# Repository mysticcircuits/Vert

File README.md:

# Vert
files for the Vert Eurorack module by Mystic Circuits.

This module comes with an open source licence, CC-BY-SA 3.0.  Go ahead and read the licence page for more details. This means that there are no commercial restrictions on this module.  Please be reasonable in your interpretation of this rule.  I fully support people building their own circuit boards and even trading amongst their friends for them.  However organizing group buys for these PCBs or selling the PCBs on your own will compete directly with my own products, since I sell PCBs on my website and also provide the build documentation and support.  In short - don't be a shmuck about it or else I will stop open sourcing my designs.

Also note that this module is made to function with my "Universal Front Plate" PCB which is hosted in another branch.  It can make the schematic a bit tricky to read sometimes but I did my best to annotate things.  There *might* be some inconsistencies between the pin naming convention for this schematic and the one on the "UFP" schematic because this was the first circuit that I build to work with the UFP and they both went through several revisions together.

For a description of the licence in simple terms please visit https://creativecommons.org/licenses/by-sa/3.0/

*************************************************************************************BUILD INSTRUCTIONS

Here is a link to the instructions.  Please look them over before you attempt to build a Vert and make sure that it is within your skill level.  The Vert is an intermediate build and involves SMD soldering.  I would definitely not attempt to build it as your first project.

https://drive.google.com/file/d/0B1jw1Qp2qZVJNUZ4QTZxX2lhblk/view?usp=sharing

Here is a link to the mouser cart.  Please note that it does not include several components and is also designed to build a VERT with all white LEDs.  Also be aware that I have noticed different behavior between different 555 timer IC models, the model included in the cart is the one that I use because it is stable.

http://www.mouser.com/ProjectManager/ProjectDetail.aspx?AccessID=2263e5f92d

There are two sources for the hardware, unfortunately you can not buy all of what you need from either place:

For the jacks go to either Thonk or Modular Addict.  You need 11 of the the "erthenvar" aka PJ301BM jacks.  Make sure to get nuts along with them, you might have to buy them separately.  Knurled or hex are both fine it's up to you.

https://www.thonk.co.uk/shop/3-5mm-jacks/

https://modularaddict.com/parts/jacks/pj301bm-jacks

You can also buy the vertical PCB mount alpha pots from Thonk/ Modularaddict or Small Bear.  Its way cheaper than buying them from Mouser

1M LINEAR POT x1

100K LINEAR POT x2

https://www.thonk.co.uk/shop/alpha-9mm-pots/

https://modularaddict.com/parts/potentiometers-1/9mm-potentiometers

http://smallbear-electronics.mybigcommerce.com/alpha-single-gang-9mm-right-angle-pc-mount/

Here are the links for the Small Bear parts.  You can buy SPDT switches from a variety of places but I highly suggest buying the short bat toggles listed below.  The switches go in between the pots and so if the bats are too long they will interfere with your ability to turn the knobs comfortably.  I haven't personally tried the Tayda toggle switches but see no reason that they wouldn't work.  If you try them out please let me know how it goes so I can confirm whether or not they are a good choice.

http://smallbear-electronics.mybigcommerce.com/spdt-on-on-0218b/

https://www.taydaelectronics.com/electromechanical/switches-key-pad/toggle-switch/mini-toggle-switch-1m-series-spdt-on-on-short-lever.html

I also buy my purple knobs from Small Bear but any knobs that fit a smooth pot shaft will do.  If you want to use knobs for knurled or D-pot shafts obviously you just have to find the corresponding shaft to replace mine.  I like these pots because they are thin, the painted indicator is inlayed so it wont rub off, and the knurl feels good on the finger.

http://smallbear-electronics.mybigcommerce.com/knurled-silver-center-colors/

https://www.thonk.co.uk/shop/knobs-davies-1900h-clone-metal/

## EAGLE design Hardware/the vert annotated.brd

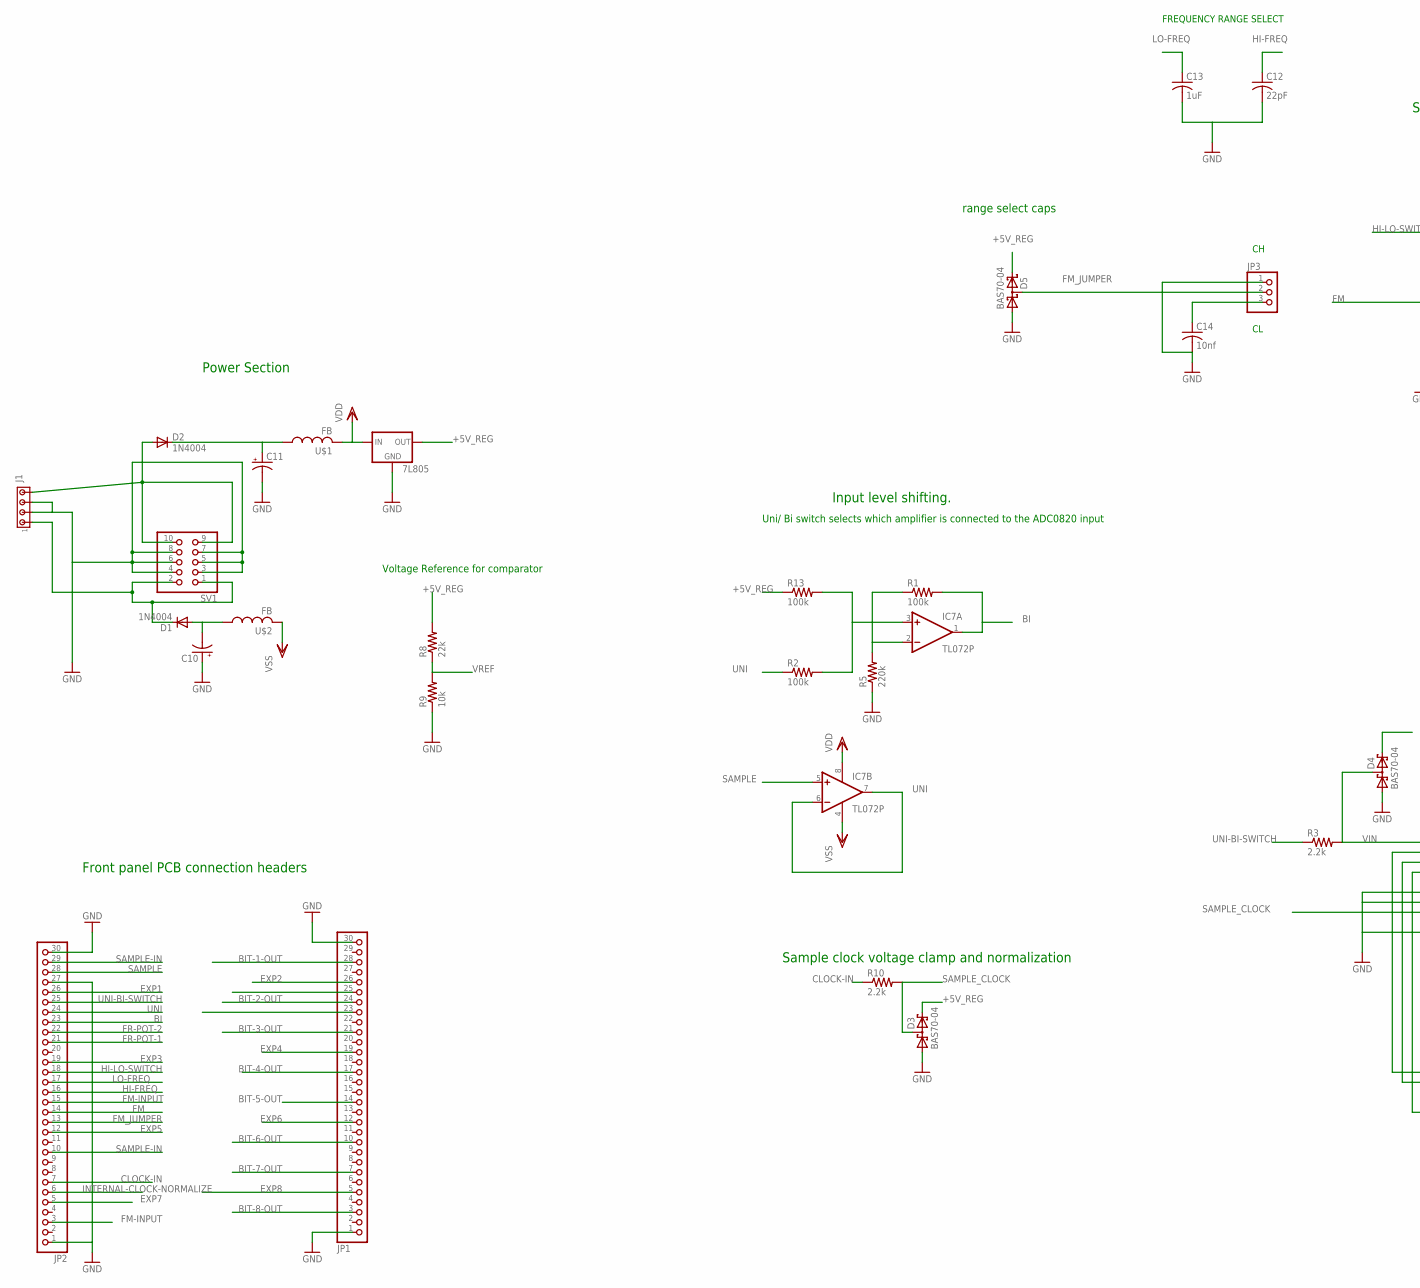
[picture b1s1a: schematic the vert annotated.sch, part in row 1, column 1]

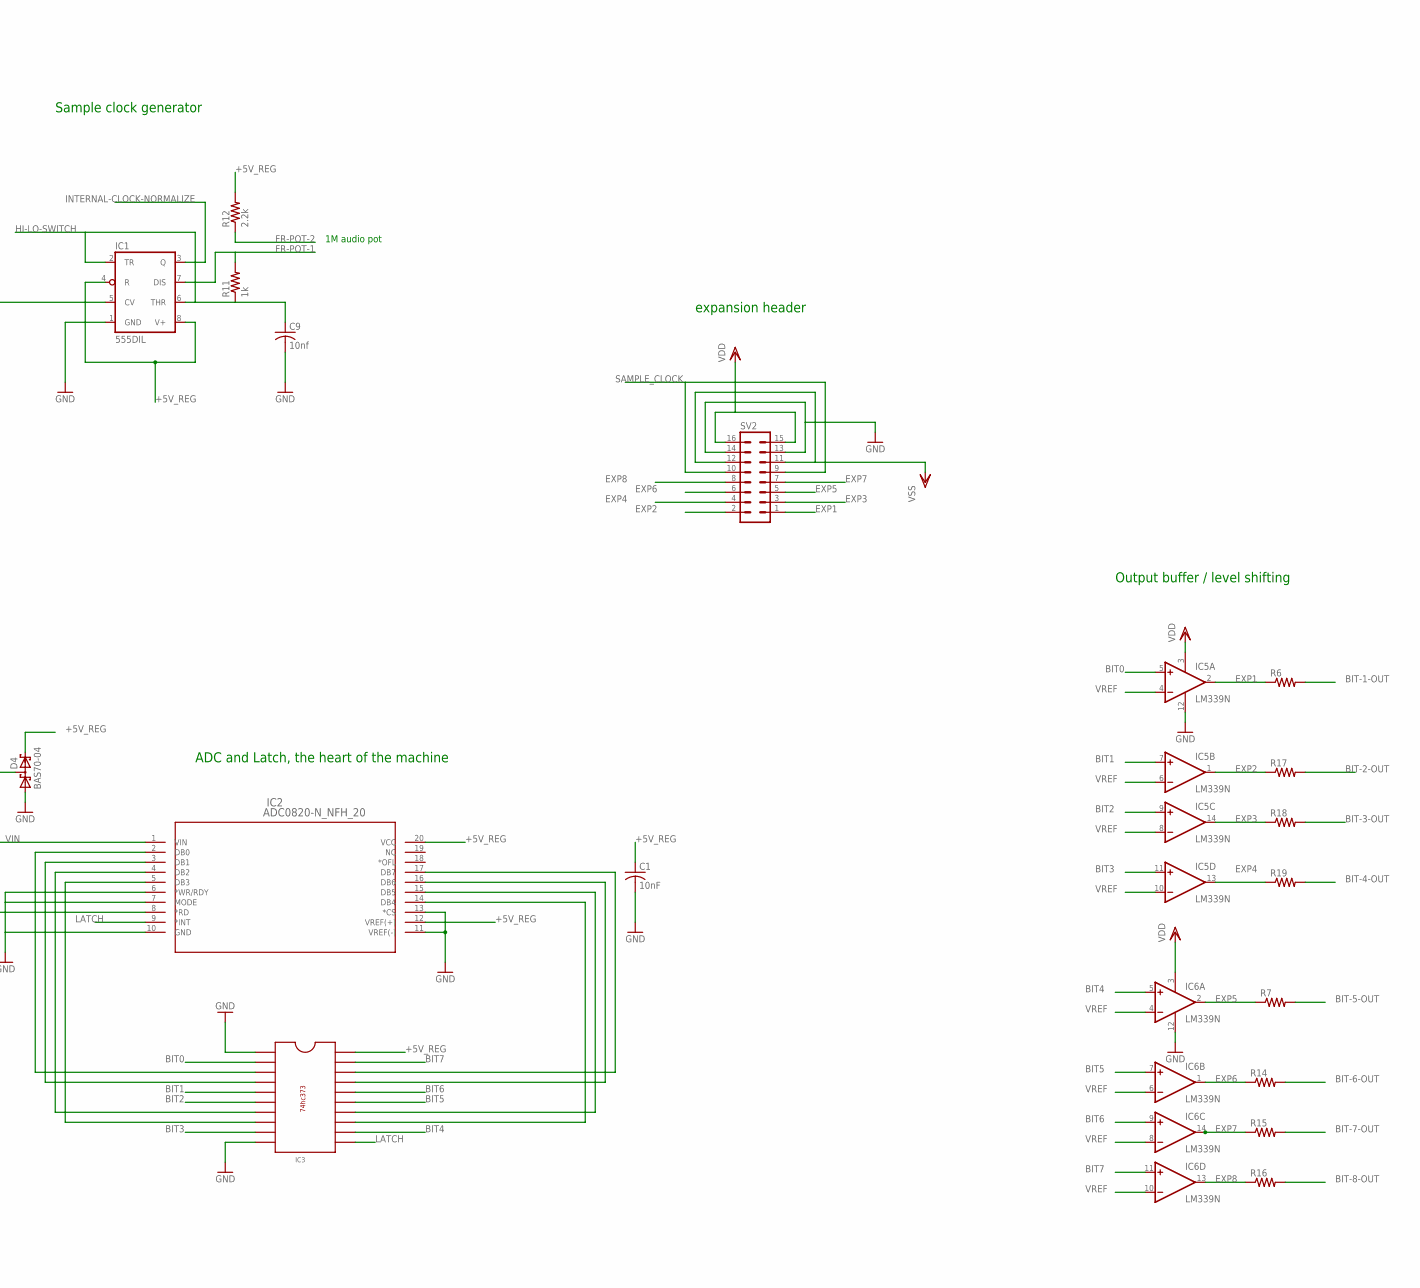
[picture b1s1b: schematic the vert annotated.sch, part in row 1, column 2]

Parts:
7L805: 78LXX
C1: 10nF; C1206
C9, C14: 10nf; C1206
C10, C11: CPOL-USE5-5; E5-5
C12: 22pF; C1206
C13: 1uF; C1206
D1, D2: 1N4004; DO41-10
D3, D4, D5: BAS70-04; SOT23
IC1: 555DIL; DIL08
IC2: ADC0820-N_NFH_20; NFH20
IC3: 74HC373; DIL20
IC5, IC6: LM339N; DIL14
IC7: TL072P; DIL08
J1: MTA04-156; 1X4MTA
JP1, JP2: PINHD-1X30; 1X30
JP3: PINHD-1X3; 1X03
R1, R2, R13: 100k; R1206
R3, R10, R12: 2.2k; R1206
R5: 220k; R1206
R6, R7, R14, R15, R16, R17, R18, R19: R-US_R1206; R1206
R8: 22k; R1206
R9: 10k; R1206
R11: 1k; R1206
SV1: PINHD-2X5; 2X05
SV2: MA08-2
U$1, U$2: FB

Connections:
+5V_REG: 7L805.OUT, C1.1, D3.2 (C2), D4.2 (C2), D5.2 (C2), IC1.4 (R), IC1.8 (V+), IC2.12 (VREF(+)), IC2.20 (VCC), IC3.20, R8.2, R12.2, R13.1
BI: IC7.1 (OUT), JP2.23, R1.2
BIT0: IC3.2, IC5.5 (+IN)
BIT1: IC3.5, IC5.7 (+IN)
BIT2: IC3.6, IC5.9 (+IN)
BIT3: IC3.9, IC5.11 (+IN)
BIT4: IC3.12, IC6.5 (+IN)
BIT5: IC3.15, IC6.7 (+IN)
BIT6: IC3.16, IC6.9 (+IN)
BIT7: IC3.19, IC6.11 (+IN)
BIT-1-OUT: JP1.28, R6.2
BIT-2-OUT: JP1.24, R17.2
BIT-3-OUT: JP1.21, R18.2
BIT-4-OUT: JP1.17, R19.2
BIT-5-OUT: JP1.14, R7.2
BIT-6-OUT: JP1.10, R14.2
BIT-7-OUT: JP1.7, R15.2
BIT-8-OUT: JP1.3, R16.2
CLOCK-IN: JP2.7, R10.1
EXP1: IC5.2 (OUT), JP2.26, R6.1, SV2.1
EXP2: IC5.1 (OUT), JP1.26, R17.1, SV2.2
EXP3: IC5.14 (OUT), JP2.19, R18.1, SV2.3
EXP4: IC5.13 (OUT), JP1.19, R19.1, SV2.4
EXP5: IC6.2 (OUT), JP2.12, R7.1, SV2.5
EXP6: IC6.1 (OUT), JP1.12, R14.1, SV2.6
EXP7: IC6.14 (OUT), JP2.5, R15.1, SV2.7
EXP8: IC6.13 (OUT), JP1.5, R16.1, SV2.8
FM: IC1.5 (CV), JP2.14
FM-INPUT: JP2.3, JP2.15
FM_JUMPER: D5.3 (C1A2), JP2.13, JP3.2
FR-POT-1: IC1.7 (DIS), JP2.21, R11.2
FR-POT-2: JP2.22, R12.1
GND: 7L805.GND, C1.2, C9.2, C10.+, C11.-, C12.2, C13.2, C14.2, D3.1 (A1), D4.1 (A1), D5.1 (A1), IC1.1 (GND), IC2.6 (*WR/RDY), IC2.7 (MODE), IC2.10 (GND), IC2.11 (VREF(-)), IC2.13 (*CS), IC3.1, IC3.10, IC5.12 (GND), IC6.12 (GND), J1.2, J1.3, JP1.1, JP1.30, JP2.1, JP2.27, JP2.30, JP3.1, R5.1, R9.1, SV1.3, SV1.4, SV1.5, SV1.6, SV1.7, SV1.8, SV2.13, SV2.14
HI-FREQ: C12.1, JP2.16
HI-LO-SWITCH: C9.1, IC1.2 (TR), IC1.6 (THR), JP2.18, R11.1
INTERNAL-CLOCK-NORMALIZE: IC1.3 (Q), JP2.6
LATCH: IC2.9 (*INT), IC3.11
LO-FREQ: C13.1, JP2.17
unnamed: D2.A, J1.4, SV1.9, SV1.10
unnamed: C14.1, JP3.3
unnamed: IC7.2 (-IN), R1.1, R5.2
unnamed: D1.C, J1.1, SV1.1, SV1.2
unnamed: C11.+, D2.C, U$1.P$1 (1)
unnamed: IC2.2 (DB0), IC3.3
unnamed: C10.-, D1.A, U$2.P$1 (1)
unnamed: IC7.3 (+IN), R2.2, R13.2
unnamed: IC2.3 (DB1), IC3.4
unnamed: IC2.4 (DB2), IC3.7
unnamed: IC2.5 (DB3), IC3.8
unnamed: IC2.17 (DB7), IC3.18
unnamed: IC2.16 (DB6), IC3.17
unnamed: IC2.15 (DB5), IC3.14
unnamed: IC2.14 (DB4), IC3.13
R-NC-2: JP1.25
R-SW-2: JP1.23
SAMPLE: IC7.5 (+IN), JP2.28
SAMPLE-IN: JP2.10, JP2.29
SAMPLE_CLOCK: D3.3 (C1A2), IC2.8 (*RD), R10.2, SV2.9, SV2.10
UNI: IC7.6 (-IN), IC7.7 (OUT), JP2.24, R2.1
UNI-BI-SWITCH: JP2.25, R3.1
VDD: 7L805.IN, IC5.3 (V+), IC6.3 (V+), IC7.8 (V+), SV2.15, SV2.16, U$1.P$2 (2)
VIN: D4.3 (C1A2), IC2.1 (VIN), R3.2
VREF: IC5.4 (-IN), IC5.6 (-IN), IC5.8 (-IN), IC5.10 (-IN), IC6.4 (-IN), IC6.6 (-IN), IC6.8 (-IN), IC6.10 (-IN), R8.1, R9.2
VSS: IC7.4 (V-), SV2.11, SV2.12, U$2.P$2 (2)

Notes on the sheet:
1M audio pot
range select caps
Output buffer / level shifting
ADC and Latch, the heart of the machine
expansion header
Sample clock generator
Sample clock voltage clamp and normalization
Input level shifting.
Uni/ Bi switch selects which amplifier is connected to the ADC0820 input
Voltage Reference for comparator
Power Section
Front panel PCB connection headers
FREQUENCY RANGE SELECT

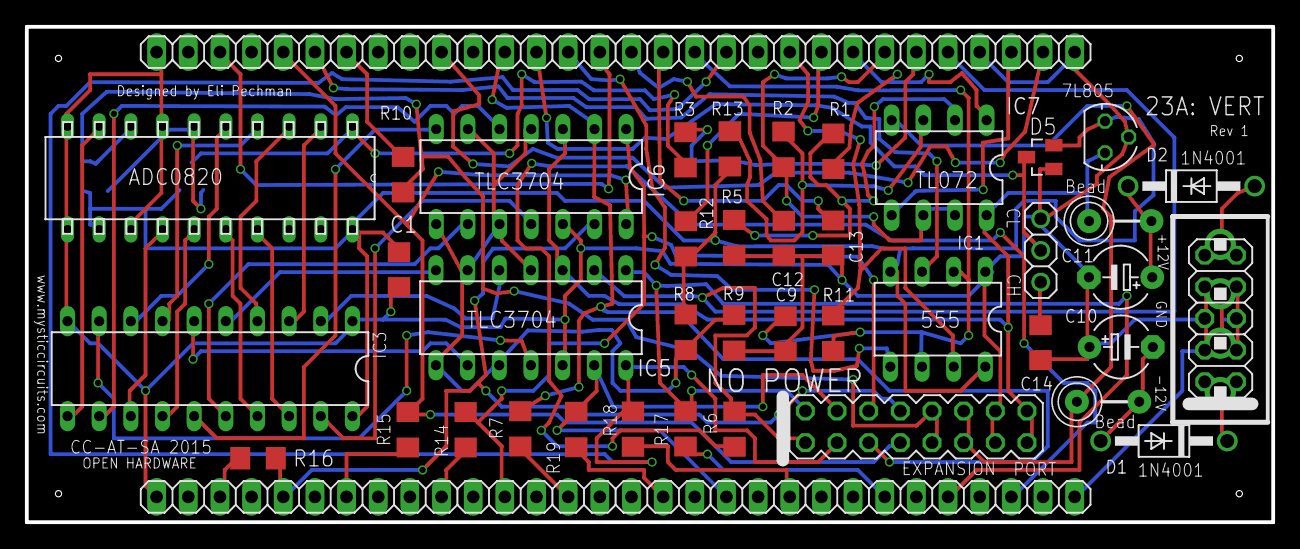
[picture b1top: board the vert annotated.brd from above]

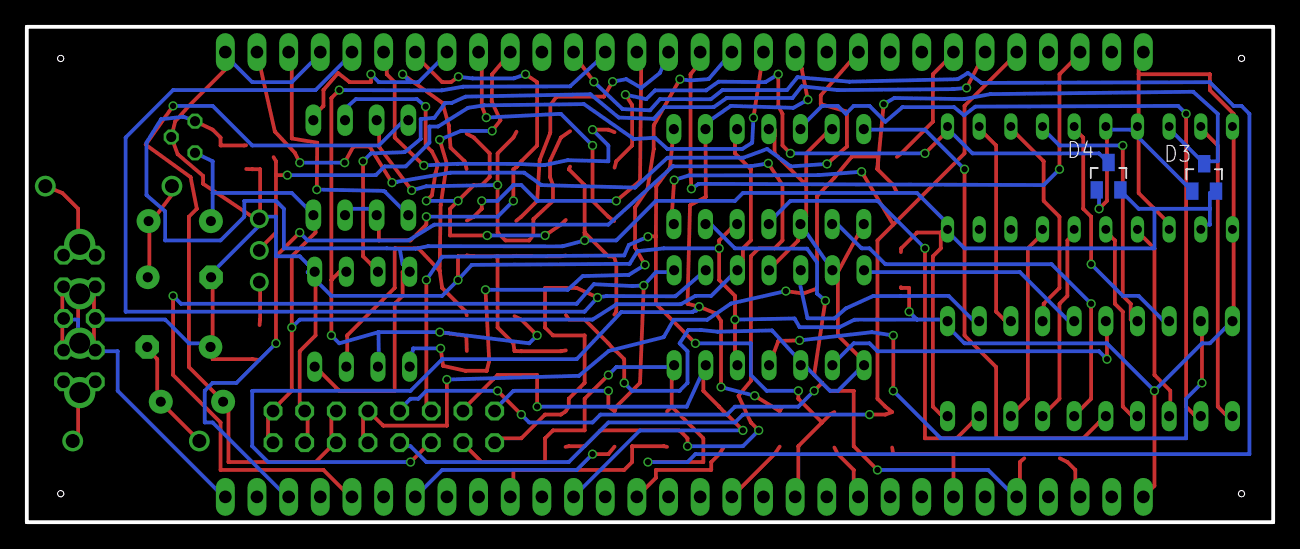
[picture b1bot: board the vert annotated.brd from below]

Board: 2 copper layers, 100.0 x 39.7 mm, 45 parts (2 on the bottom side), 62 nets.

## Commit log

2016-05-03 Create licence
2016-05-03 Added files via upload
2016-05-03 Create blah
